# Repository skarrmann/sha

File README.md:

# Sha Keyboard

Sha is a 50 key ortholinear keyboard, powered by either a [Waveshare RP2040-Zero](https://www.waveshare.com/rp2040-zero.htm) or [Waveshare RP2040-Matrix](https://www.waveshare.com/product/rp2040-matrix.htm).

## Project structure

* [`gerbers`](gerbers): Gerber files for PCB manufacturing
* [`graphics`](graphics): Source assets for PCB silkscreen
* [`kicad`](kicad): KiCad project files (schematics and PCB designs)
* [`kicad-libraries`](kicad-libraries): KiCad components and footprints
* [`images`](images): Images for project documentation
* [`firmware`](firmware): Firmware files

## PCBs

Two separate PCB designs are available for MX and Choc keyswitches, with their respective footprints and key spacing (MX: 19mm x 19mm, Choc: 18mm x 17mm).

The Waveshare RP2040-Zero/Matrix footprint uses surface-mount solder pads. The castellated pads of the MCU board are soldered directly onto the PCB.

**Each build uses two copies of the main PCB**. This PCB acts as both the logical PCB, and when flipped the long way, it acts as a bottom plate to be attached the logical PCB.

An optional top plate PCB is available in the gerber files. This top plate covers the diodes and the solder pads of the MCU board.

## Keyboard firmware

* KMK
    * Setup instructions and basic configuration is in this repo: [`firmware/kmk`](firmware/kmk)
* [QMK](https://github.com/qmk/qmk_firmware/tree/master/keyboards/sha)

## Bill of materials

Part | Purpose | Quantity | Notes
---- | ------- | -------- | -----
Main PCB  | circuit board and bottom plate | 2 | Send Gerber zip files to [JLCPCB](https://jlcpcb.com/)
Top plate PCB | protects diodes and MCU board | 1 |
Waveshare RP2040-Zero | Microcontroller board | 1 | Also supports Waveshare RP2040-Matrix
1N4148 SOD-123 | Diodes for keyboard row-column matrix | 50 |
Keyswitches |  | 50 | PCB mount (5 pin) switches recommended. For MX, any switches should work. For Choc, get Choc V1 switches.
Keycaps |  | 50 | For MX, any keycaps should work. For Choc, get those which fit Choc V1 18mm x 17mm
M2 6mm screws | 4 to secure main PCB and bottom plate PCB, 4 for top plate | 8 |
M2 nuts | 4 to secure main PCB and bottom plate PCB, 4 as spacers for top plate | 8 |
2mm tall rubber bumpons | Raise board above desk surface and provide skid resitance | 8 | 

Note the 4 M2 6mm screws and 4 M2 nuts just "friction fit" the top plate. To fully screw in the top plate, You could use 4 M2 8mm+ screws and 4 more M2 nuts. I meant to do this, but accidentally ordered the wrong size screws...!

## PCB manufacturing settings

These are the manufacturing settings I used when ordering from JLCPCB:

* **Base Material**: FR4
* **Layers**: 2
* **Dimensions**: (whatever the gerber file specifies)
* **PCB Qty**: 5
* **Different Design**: 1
* **Delivery Format**: Single PCB
* **PCB Thickness**: 1.6
* **PCB Color**: Black
* **Silkscreen**: White
* **Surface Finish**: LeadFree HASL-RoHS
* **Outer Copper Weight**: 1 oz
* **Gold Fingers**: No
* **Confirm Production File**: No
* **Flying Probe Test**: Fully Test
* **Castellated Holes**: No
* **Remove Order Number**: Specify a location

**IMPORTANT:** The PCB has ["JLCJLCJLCJLC" silkscreen text](https://jlcpcb.com/help/article/50-How-to-remove-order-number-from-your-PCB) on top side of the board. If you want to remove the order number from the boards or you want to print the PCBs with another manufacturer, then I recommend removing this silkscreen text from the `.kicad_pcb` file, and then regenerate the Gerber files.

## Build tips

* Solder the diodes first. Tin one side of all the diode solder pads, and then position each diode and re-heat this tinned pad to tack the diode in place. Then solder the other diode leg on each diode.
     * 
* Once the diodes are fully soldered, do the microcontroller board next. Tape the board into position, and then solder the corner pads to tack it into place. Remove the tape and solder the remaining microcontroller board pads.
     * 
* Last, solder in the switches. Note the switch PCB mounting pin holes were loose on my PCBs, but this might have been a manufacturing anomaly since I've never encountered this issue in other builds using this footprint. I worked around this by placing keycaps on the switches, then first soldering the four corner switches while applying pressure on top of the switch so it's fully inserted. Then I placed all the switches in their slots, pressed a spare PCB on top of the switches in a sandwich, flipped the board over, and soldered one leg of each switch while applying pressure to fully insert the switches. After confirming the switches were fully inserted, I soldered the other leg on each switch.
     * 
* For attaching the plates, use a single screw and hex nut to secure the bottom plate PCB to the main PCB. For the top plate, I just put a 6mm screw and hex through this plate's holes. The screw threads rest inside the PCB mounting holes, giving it a fiction fit. You could use other hardware to permanently screw in the top plate. See the BOM notes for suggestions.
     * 
     * 

## KiCad project notes

The top plate was generated with the [Horizon Board Producer KiCad plugin](https://github.com/skarrmann/horizon#kicad-project-notes).

## Revision history

* **Sha 1.0** (2023-11-26)
     * Initial MX switch PCB design
* **Sha 1.1** (2024-10-09)
     * Create Choc switch PCB design
     * Update logos

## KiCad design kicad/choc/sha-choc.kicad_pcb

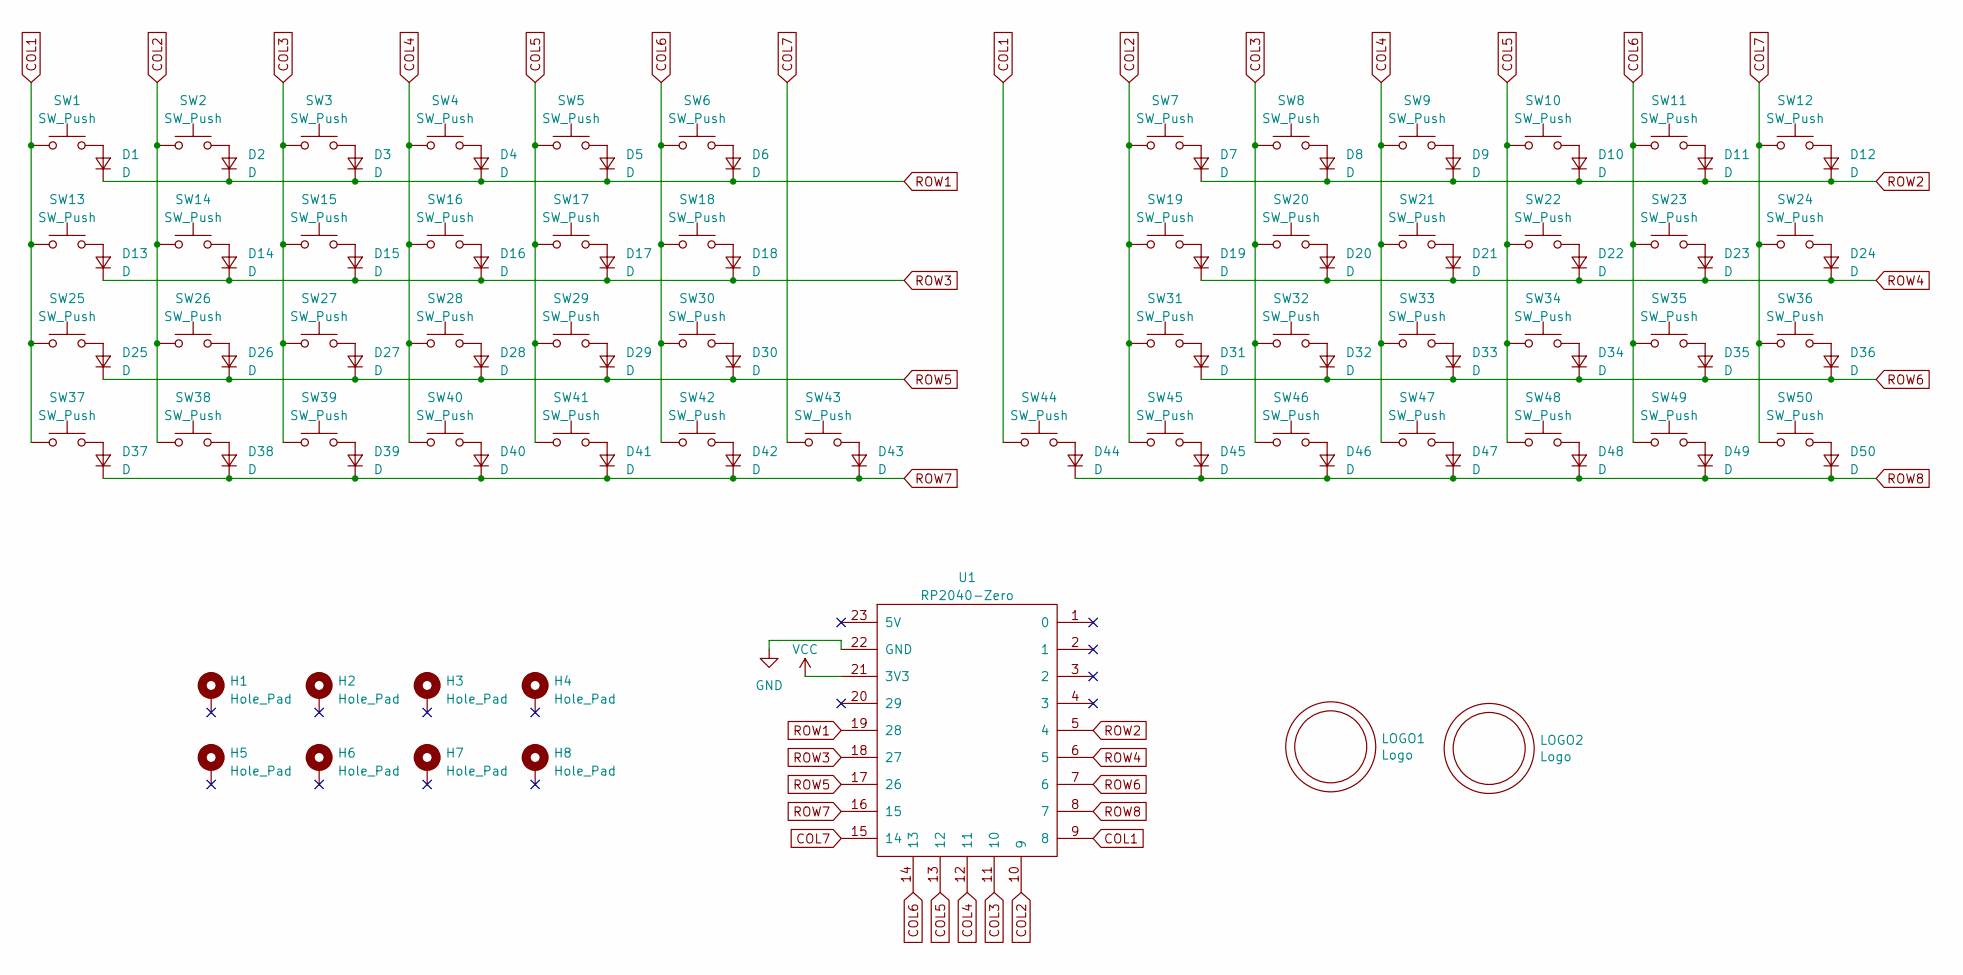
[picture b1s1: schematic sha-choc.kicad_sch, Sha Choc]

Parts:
D1, D2, D3, D4, D5, D6, D7, D8, D9, D10, D11, D12, D13, D14, D15, D16, D17, D18, D19, D20, D21, D22, D23, D24, D25, D26, D27, D28, D29, D30, D31, D32, D33, D34, D35, D36, D37, D38, D39, D40, D41, D42, D43, D44, D45, D46, D47, D48, D49, D50: D; D_SOD-123
H1, H2, H3, H4, H5, H6, H7, H8: Hole_Pad; Mount_M2
LOGO1: Logo; Logo_Sha
LOGO2: Logo; Logo_Sha_Name
SW1, SW2, SW3, SW4, SW5, SW6, SW7, SW8, SW9, SW10, SW11, SW12, SW13, SW14, SW15, SW16, SW17, SW18, SW19, SW20, SW21, SW22, SW23, SW24, SW25, SW26, SW27, SW28, SW29, SW30, SW31, SW32, SW33, SW34, SW35, SW36, SW37, SW38, SW39, SW40, SW41, SW42, SW43, SW44, SW45, SW46, SW47, SW48, SW49, SW50: SW_Push; SW_Choc_Reverse_Cutout
U1: RP2040-Zero; RP2040-Zero_SMD

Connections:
COL1: SW1.1, SW13.1, SW25.1, SW37.1, SW44.1, U1.9 (8)
COL2: SW2.1, SW7.1, SW14.1, SW19.1, SW26.1, SW31.1, SW38.1, SW45.1, U1.10 (9)
COL3: SW3.1, SW8.1, SW15.1, SW20.1, SW27.1, SW32.1, SW39.1, SW46.1, U1.11 (10)
COL4: SW4.1, SW9.1, SW16.1, SW21.1, SW28.1, SW33.1, SW40.1, SW47.1, U1.12 (11)
COL5: SW5.1, SW10.1, SW17.1, SW22.1, SW29.1, SW34.1, SW41.1, SW48.1, U1.13 (12)
COL6: SW6.1, SW11.1, SW18.1, SW23.1, SW30.1, SW35.1, SW42.1, SW49.1, U1.14 (13)
COL7: SW12.1, SW24.1, SW36.1, SW43.1, SW50.1, U1.15 (14)
GND: U1.22 (GND)
unnamed: D1.2 (A), SW1.2
unnamed: D2.2 (A), SW2.2
unnamed: D3.2 (A), SW3.2
unnamed: D4.2 (A), SW4.2
unnamed: D5.2 (A), SW5.2
unnamed: D6.2 (A), SW6.2
unnamed: D7.2 (A), SW7.2
unnamed: D8.2 (A), SW8.2
unnamed: D9.2 (A), SW9.2
unnamed: D10.2 (A), SW10.2
unnamed: D11.2 (A), SW11.2
unnamed: D12.2 (A), SW12.2
unnamed: D13.2 (A), SW13.2
unnamed: D14.2 (A), SW14.2
unnamed: D15.2 (A), SW15.2
unnamed: D16.2 (A), SW16.2
unnamed: D17.2 (A), SW17.2
unnamed: D18.2 (A), SW18.2
unnamed: D19.2 (A), SW19.2
unnamed: D20.2 (A), SW20.2
unnamed: D21.2 (A), SW21.2
unnamed: D22.2 (A), SW22.2
unnamed: D23.2 (A), SW23.2
unnamed: D24.2 (A), SW24.2
unnamed: D25.2 (A), SW25.2
unnamed: D26.2 (A), SW26.2
unnamed: D27.2 (A), SW27.2
unnamed: D28.2 (A), SW28.2
unnamed: D29.2 (A), SW29.2
unnamed: D30.2 (A), SW30.2
unnamed: D31.2 (A), SW31.2
unnamed: D32.2 (A), SW32.2
unnamed: D33.2 (A), SW33.2
unnamed: D34.2 (A), SW34.2
unnamed: D35.2 (A), SW35.2
unnamed: D36.2 (A), SW36.2
unnamed: D37.2 (A), SW37.2
unnamed: D38.2 (A), SW38.2
unnamed: D39.2 (A), SW39.2
unnamed: D40.2 (A), SW40.2
unnamed: D41.2 (A), SW41.2
unnamed: D42.2 (A), SW42.2
unnamed: D43.2 (A), SW43.2
unnamed: D44.2 (A), SW44.2
unnamed: D45.2 (A), SW45.2
unnamed: D46.2 (A), SW46.2
unnamed: D47.2 (A), SW47.2
unnamed: D48.2 (A), SW48.2
unnamed: D49.2 (A), SW49.2
unnamed: D50.2 (A), SW50.2
ROW1: D1.1 (K), D2.1 (K), D3.1 (K), D4.1 (K), D5.1 (K), D6.1 (K), U1.19 (28)
ROW2: D7.1 (K), D8.1 (K), D9.1 (K), D10.1 (K), D11.1 (K), D12.1 (K), U1.5 (4)
ROW3: D13.1 (K), D14.1 (K), D15.1 (K), D16.1 (K), D17.1 (K), D18.1 (K), U1.18 (27)
ROW4: D19.1 (K), D20.1 (K), D21.1 (K), D22.1 (K), D23.1 (K), D24.1 (K), U1.6 (5)
ROW5: D25.1 (K), D26.1 (K), D27.1 (K), D28.1 (K), D29.1 (K), D30.1 (K), U1.17 (26)
ROW6: D31.1 (K), D32.1 (K), D33.1 (K), D34.1 (K), D35.1 (K), D36.1 (K), U1.7 (6)
ROW7: D37.1 (K), D38.1 (K), D39.1 (K), D40.1 (K), D41.1 (K), D42.1 (K), D43.1 (K), U1.16 (15)
ROW8: D44.1 (K), D45.1 (K), D46.1 (K), D47.1 (K), D48.1 (K), D49.1 (K), D50.1 (K), U1.8 (7)
VCC: U1.21 (3V3)

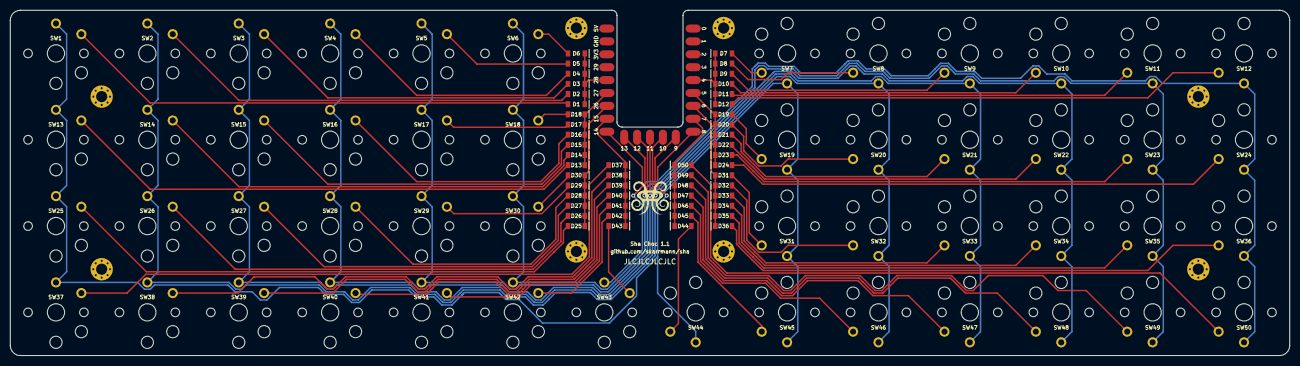
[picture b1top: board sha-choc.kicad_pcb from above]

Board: 2 copper layers, 252.0 x 68.0 mm, 111 parts (1 on the bottom side), 65 nets.

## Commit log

2023-11-27 Write readme description
2023-11-27 Clean up Sha logo
2023-11-27 Update project status, add proper Sha name logo SVG
2023-11-29 Center PCB silkscreen text
2023-12-13 Add initial KMK firmware implementation
2023-12-13 Update readme, add project photos
2023-12-13 Add layers and RGB to KMK firmware
2023-12-13 Add another bottom plate photo and clean up readme
2023-12-14 Remove KMK RGB extension for now. Update readmes
2023-12-14 Note QMK firmware coming soon
2023-12-14 Note QMK PR submitted
2023-12-15 Finish notes on mounting top plate
2024-02-12 Update QMK firmware link.
2024-10-12 Create Choc switch design, update logos
2024-10-12 Remove unneeded cutout line
